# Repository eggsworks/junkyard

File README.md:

## junkyard

A 45 percent keyboard designed to use up the the base set keys that are left over after building a 40%.

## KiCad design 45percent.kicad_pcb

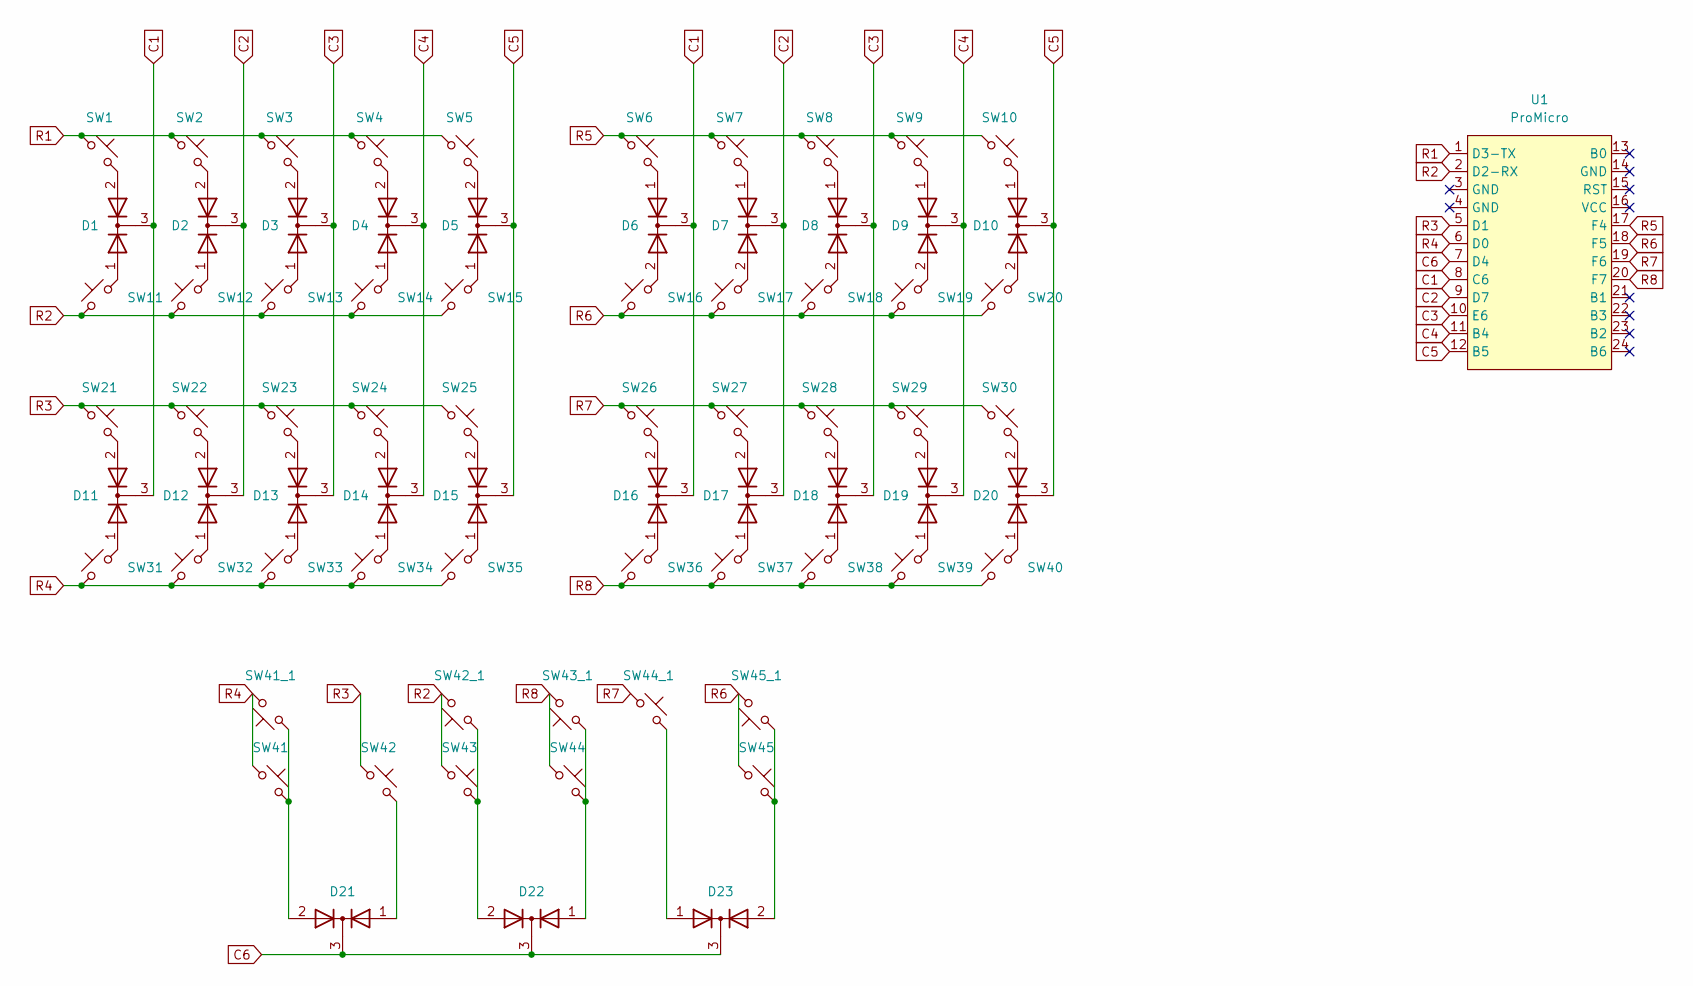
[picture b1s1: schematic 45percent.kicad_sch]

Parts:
D1, D2, D3, D4, D5, D6, D7, D8, D9, D10, D11, D12, D13, D14, D15, D16, D17, D18, D19, D20, D21, D22, D23: BAV70; SOT-23
SW1, SW2, SW3, SW4, SW5, SW6, SW7, SW8, SW9, SW10, SW11, SW12, SW13, SW14, SW15, SW16, SW17, SW18, SW19, SW20, SW21, SW22, SW23, SW24, SW25, SW26, SW27, SW28, SW29, SW30, SW31, SW32, SW33, SW34, SW35, SW36, SW37, SW38, SW39, SW40, SW41, SW41_1, SW42, SW42_1, SW43, SW43_1, SW44, SW44_1, SW45, SW45_1: SW_Push_45deg; SW_MX_1u
U1: ProMicro; ProMicro_USBup

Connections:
C1: D1.3 (K), D6.3 (K), D11.3 (K), D16.3 (K), U1.8 (C6)
C2: D2.3 (K), D7.3 (K), D12.3 (K), D17.3 (K), U1.9 (D7)
C3: D3.3 (K), D8.3 (K), D13.3 (K), D18.3 (K), U1.10 (E6)
C4: D4.3 (K), D9.3 (K), D14.3 (K), D19.3 (K), U1.11 (B4)
C5: D5.3 (K), D10.3 (K), D15.3 (K), D20.3 (K), U1.12 (B5)
C6: D21.3 (K), D22.3 (K), D23.3 (K), U1.7 (D4)
unnamed: D1.1 (A), SW11.2
unnamed: D1.2 (A), SW1.2
unnamed: D2.1 (A), SW12.2
unnamed: D2.2 (A), SW2.2
unnamed: D3.1 (A), SW13.2
unnamed: D3.2 (A), SW3.2
unnamed: D4.1 (A), SW14.2
unnamed: D4.2 (A), SW4.2
unnamed: D5.1 (A), SW15.2
unnamed: D5.2 (A), SW5.2
unnamed: D6.1 (A), SW6.2
unnamed: D6.2 (A), SW16.2
unnamed: D7.1 (A), SW7.2
unnamed: D7.2 (A), SW17.2
unnamed: D8.1 (A), SW8.2
unnamed: D8.2 (A), SW18.2
unnamed: D9.1 (A), SW9.2
unnamed: D9.2 (A), SW19.2
unnamed: D10.1 (A), SW10.2
unnamed: D10.2 (A), SW20.2
unnamed: D11.1 (A), SW31.2
unnamed: D11.2 (A), SW21.2
unnamed: D12.1 (A), SW32.2
unnamed: D12.2 (A), SW22.2
unnamed: D13.1 (A), SW33.2
unnamed: D13.2 (A), SW23.2
unnamed: D14.1 (A), SW34.2
unnamed: D14.2 (A), SW24.2
unnamed: D15.1 (A), SW35.2
unnamed: D15.2 (A), SW25.2
unnamed: D16.1 (A), SW36.2
unnamed: D16.2 (A), SW26.2
unnamed: D17.1 (A), SW37.2
unnamed: D17.2 (A), SW27.2
unnamed: D18.1 (A), SW38.2
unnamed: D18.2 (A), SW28.2
unnamed: D19.1 (A), SW39.2
unnamed: D19.2 (A), SW29.2
unnamed: D20.1 (A), SW40.2
unnamed: D20.2 (A), SW30.2
unnamed: D21.1 (A), SW42.2
unnamed: D21.2 (A), SW41.2, SW41_1.1
unnamed: D22.1 (A), SW43_1.1, SW44.2
unnamed: D22.2 (A), SW42_1.1, SW43.2
unnamed: D23.1 (A), SW44_1.2
unnamed: D23.2 (A), SW45.2, SW45_1.1
R1: SW1.1, SW2.1, SW3.1, SW4.1, SW5.1, U1.1 (D3-TX)
R2: SW11.1, SW12.1, SW13.1, SW14.1, SW15.1, SW42_1.2, SW43.1, U1.2 (D2-RX)
R3: SW21.1, SW22.1, SW23.1, SW24.1, SW25.1, SW42.1, U1.5 (D1)
R4: SW31.1, SW32.1, SW33.1, SW34.1, SW35.1, SW41.1, SW41_1.2, U1.6 (D0)
R5: SW6.1, SW7.1, SW8.1, SW9.1, SW10.1, U1.17 (F4)
R6: SW16.1, SW17.1, SW18.1, SW19.1, SW20.1, SW45.1, SW45_1.2, U1.18 (F5)
R7: SW26.1, SW27.1, SW28.1, SW29.1, SW30.1, SW44_1.1, U1.19 (F6)
R8: SW36.1, SW37.1, SW38.1, SW39.1, SW40.1, SW43_1.2, SW44.1, U1.20 (F7)

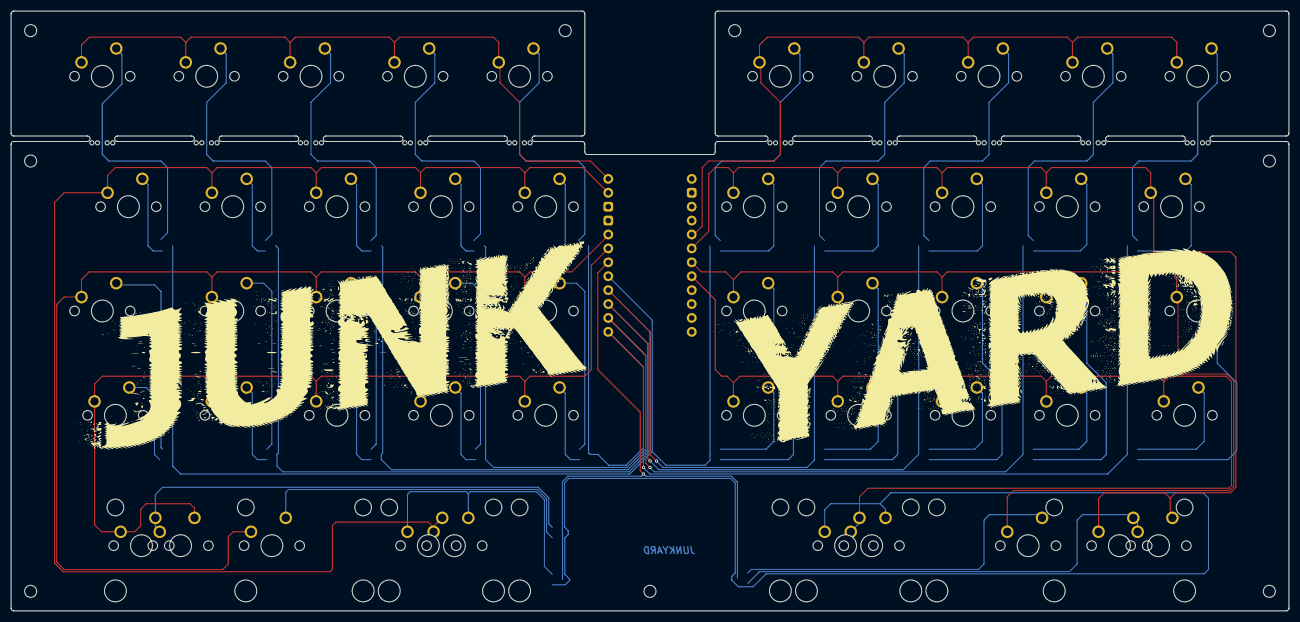
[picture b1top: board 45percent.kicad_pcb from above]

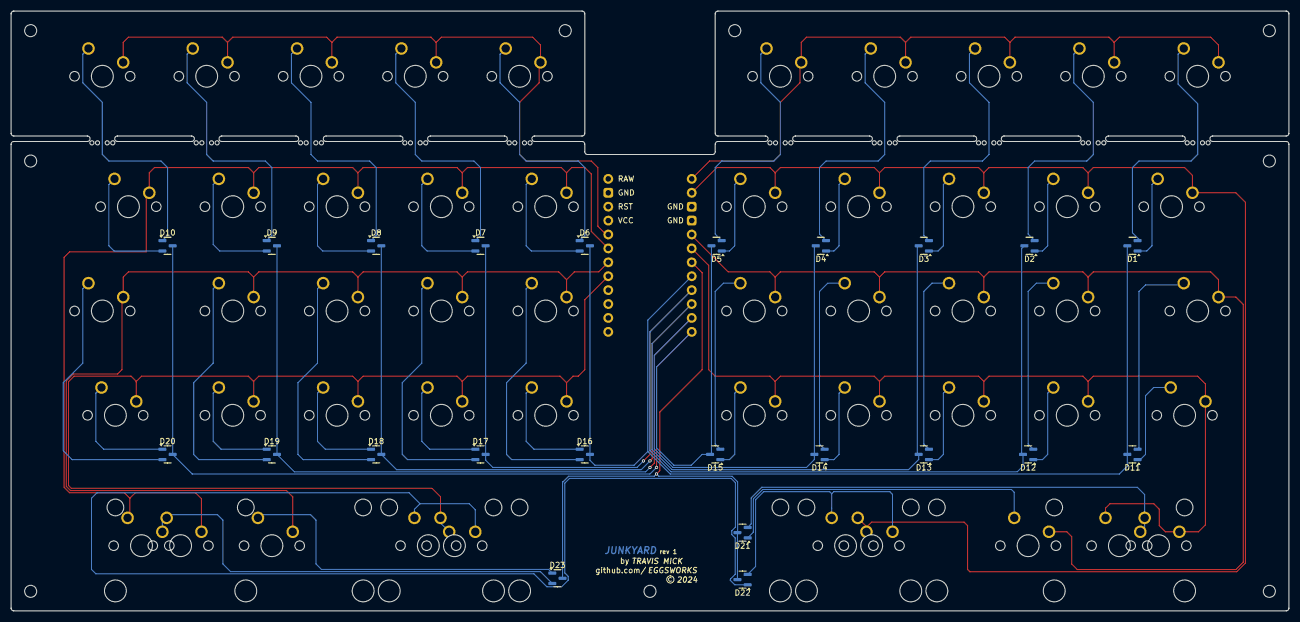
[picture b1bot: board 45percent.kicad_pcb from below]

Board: 2 copper layers, 233.4 x 109.5 mm, 74 parts (23 on the bottom side), 60 nets.
